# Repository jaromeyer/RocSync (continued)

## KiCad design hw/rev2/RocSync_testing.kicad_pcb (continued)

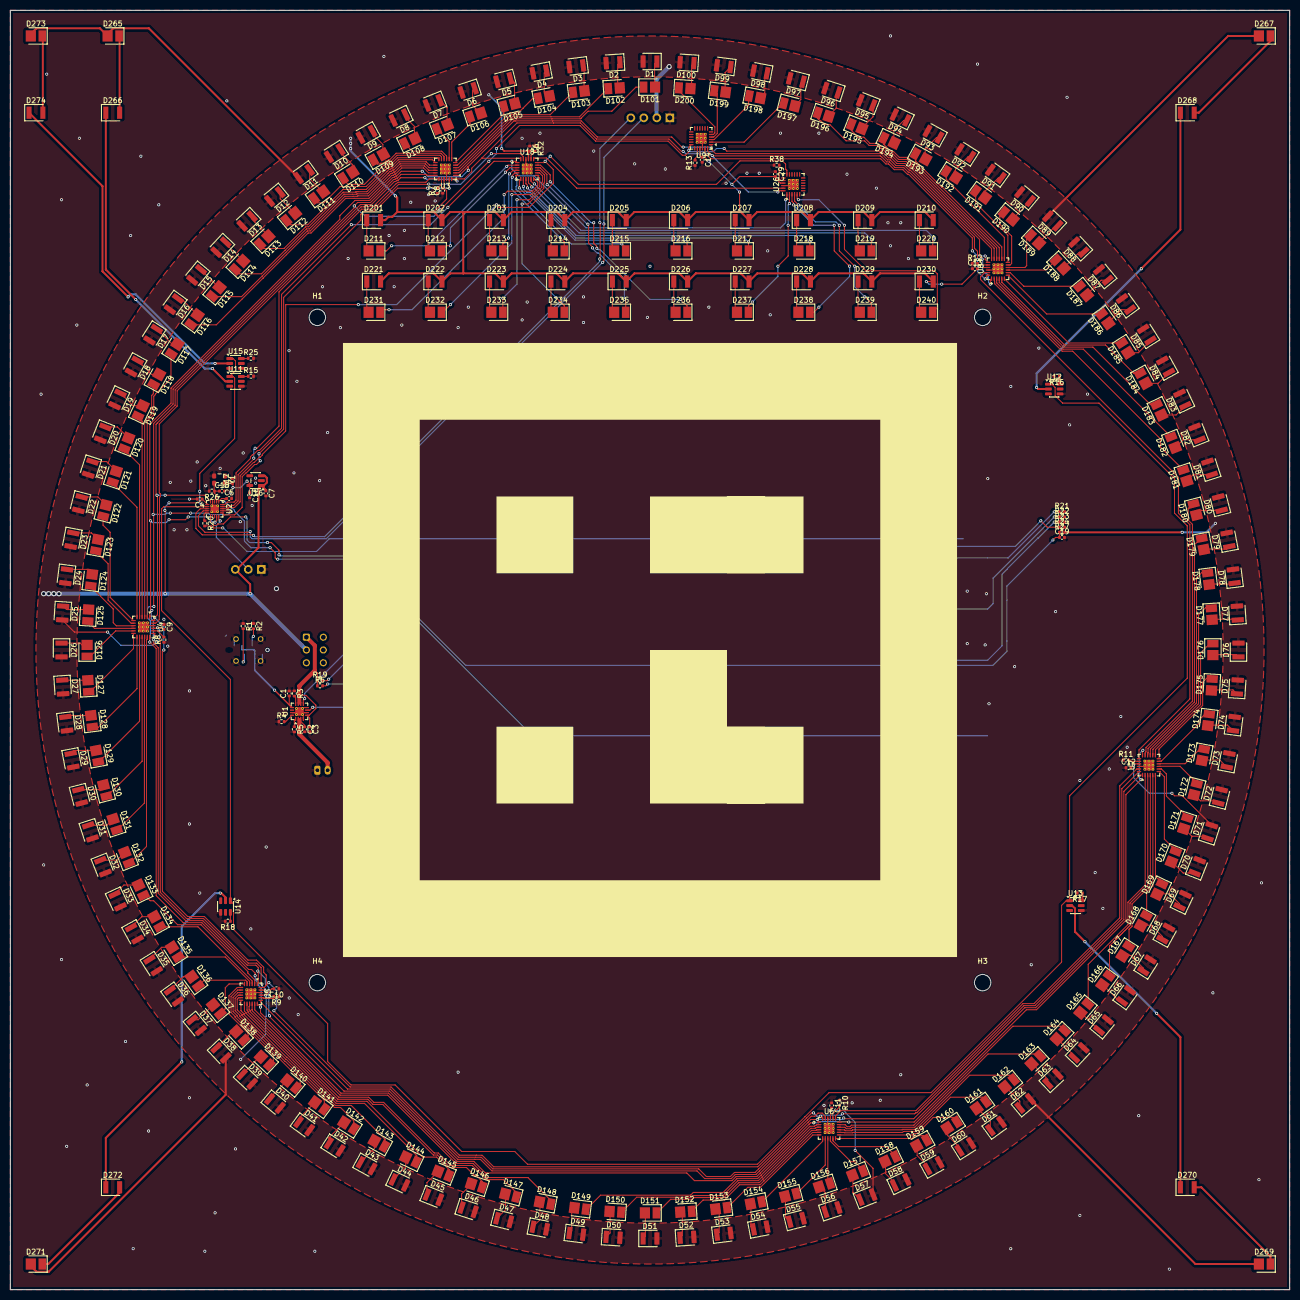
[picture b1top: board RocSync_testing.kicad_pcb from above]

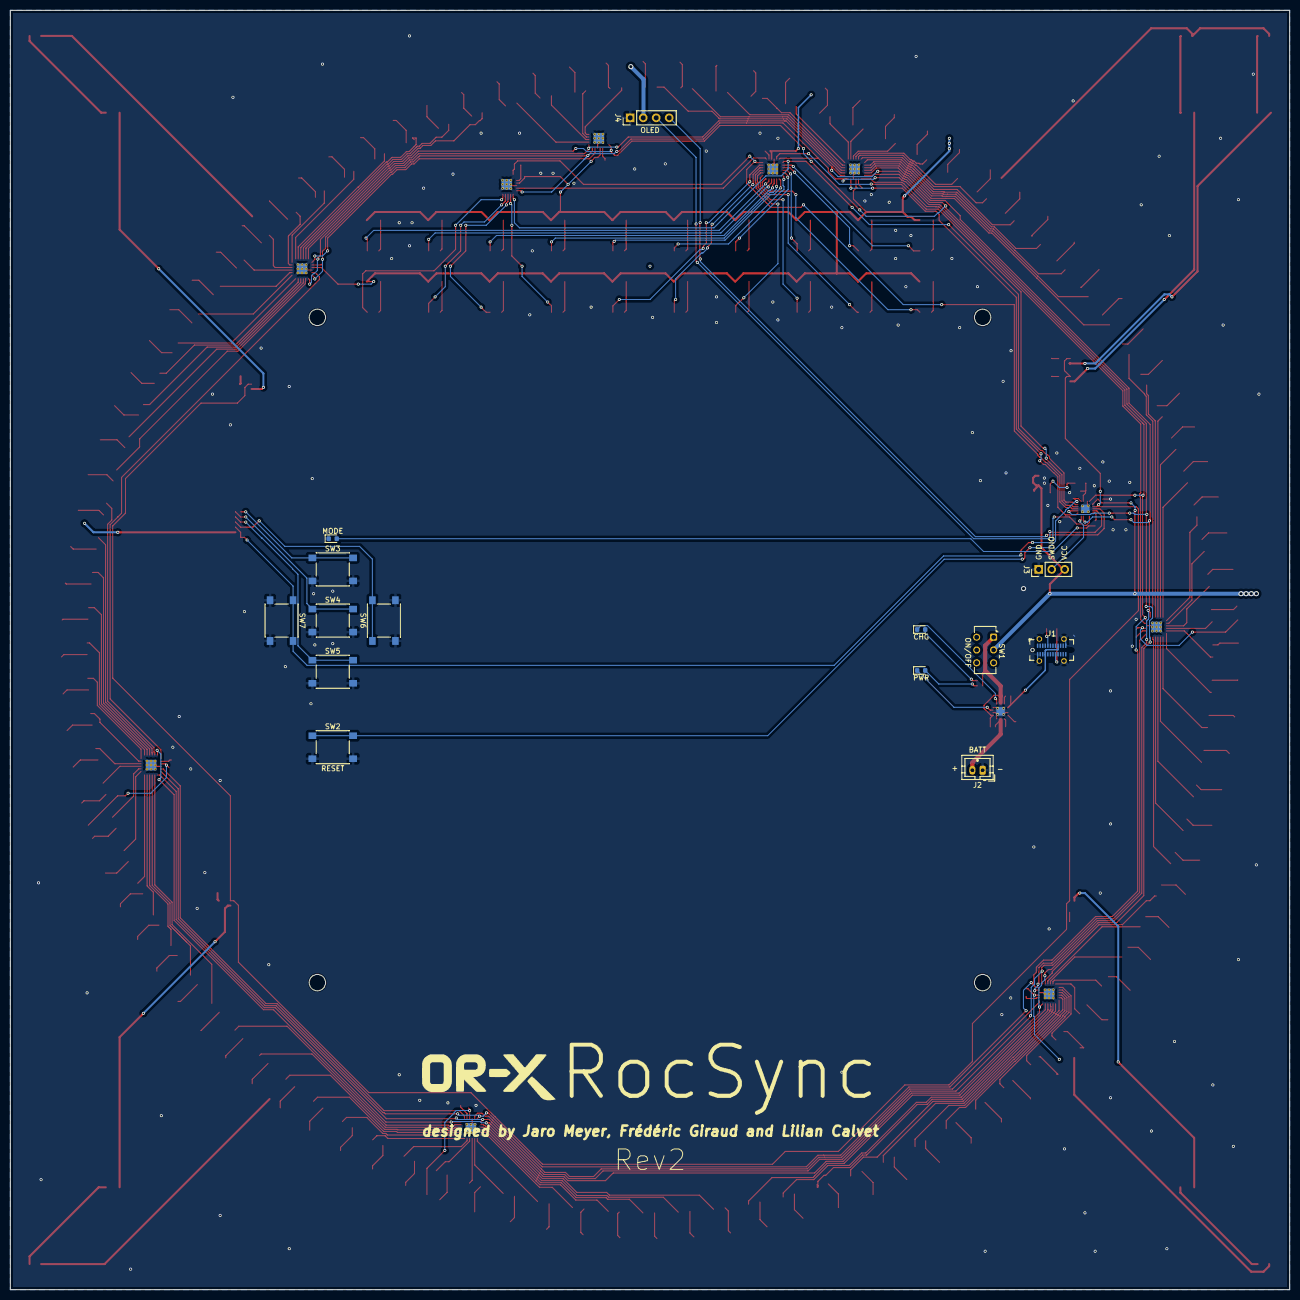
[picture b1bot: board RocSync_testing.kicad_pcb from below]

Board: 2 copper layers, 250.0 x 250.0 mm, 333 parts (14 on the bottom side), 306 nets.

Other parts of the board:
H1, H2, H3, H4: MountingHole; MountingHole_3.2mm_M3

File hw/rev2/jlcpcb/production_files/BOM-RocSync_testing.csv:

Comment,Designator,Footprint,LCSC,Quantity
0.1uf,"C10,C11,C12,C13,C14,C19,C29,C4,C5,C6,C8,C9",C_0402_1005Metric,C1525,12
1.1k,R3,R_0402_1005Metric,C25860,1
1.5k,"R19,R20,R6",R_0402_1005Metric,C25867,3
1.8k,R22,R_0402_1005Metric,C25871,1
100,"R15,R16,R17,R18,R25",R_0402_1005Metric,C25076,5
10k,"R26,R5",R_0402_1005Metric,C25744,2
10nF,C17,C_0402_1005Metric,C15195,1
10pF,C18,C_0402_1005Metric,C32949,1
1uf,"C1,C16,C7",C_0402_1005Metric,C52923,3
2.7k,"R10,R11,R12,R13,R32,R38,R7,R8,R9",R_0402_1005Metric,C25885,9
2k,R27,R_0402_1005Metric,C4109,1
4.7uf,"C2,C3",C_0402_1005Metric,C23733,2
5.1k,"R1,R2,R21",R_0402_1005Metric,C25905,3
510,R24,R_0402_1005Metric,C25123,1
590,R4,R_0402_1005Metric,C2998181,1
820,R23,R_0402_1005Metric,C25135,1
BATT,J2,JST_PH_B2B-PH-K_1x02_P2.00mm_Vertical,C594142,1
BCR420UW6Q,"U11,U12,U13,U14,U15",SOT-23-6,C194381,5
BQ24075RGT,U1,VQFN-16-1EP_3x3mm_P0.5mm_EP1.68x1.68mm_ThermalVias,C15464,1
CH32V003FxUx,U2,QFN-20-1EP_3x3mm_P0.4mm_EP1.65x1.65mm_ThermalVias,C5299908,1
CHG,D276,LED_0603_1608Metric,C2286,1
Conn_01x03_Pin,J3,PinHeader_1x03_P2.54mm_Vertical,C6332196,1
IR LED,"D101,D102,D103,D104,D105,D106,D107,D108,D109,D110,D111,D112,D113,D114,D115,D116,D117,D118,D119,D120,D121,D122,D123,D124,D125,D126,D127,D128,D129,D130,D131,D132,D133,D134,D135,D136,D137,D138,D139,D140,D141,D142,D143,D144,D145,D146,D147,D148,D149,D150,D151,D152,D153,D154,D155,D156,D157,D158,D159,D160,D161,D162,D163,D164,D165,D166,D167,D168,D169,D170,D171,D172,D173,D174,D175,D176,D177,D178,D179,D180,D181,D182,D183,D184,D185,D186,D187,D188,D189,D190,D191,D192,D193,D194,D195,D196,D197,D198,D199,D200,D211,D212,D213,D214,D215,D216,D217,D218,D219,D220,D231,D232,D233,D234,D235,D236,D237,D238,D239,D240,D265,D267,D269,D271,D273",XYC-HIR76C-LX4,C2988728,125
LED,"D1,D10,D100,D11,D12,D13,D14,D15,D16,D17,D18,D19,D2,D20,D201,D202,D203,D204,D205,D206,D207,D208,D209,D21,D210,D22,D221,D222,D223,D224,D225,D226,D227,D228,D229,D23,D230,D24,D25,D26,D266,D268,D27,D270,D272,D274,D28,D29,D3,D30,D31,D32,D33,D34,D35,D36,D37,D38,D39,D4,D40,D41,D42,D43,D44,D45,D46,D47,D48,D49,D5,D50,D51,D52,D53,D54,D55,D56,D57,D58,D59,D6,D60,D61,D62,D63,D64,D65,D66,D67,D68,D69,D7,D70,D71,D72,D73,D74,D75,D76,D77,D78,D79,D8,D80,D81,D82,D83,D84,D85,D86,D87,D88,D89,D9,D90,D91,D92,D93,D94,D95,D96,D97,D98,D99",HL-A-3528,C516141,125
MODE,D277,LED_0603_1608Metric,C2288,1
ON/OFF,SW1,SW_CK_JS202011CQN_DPDT_Straight,C431542,1
PWR,D275,LED_0603_1608Metric,C2288,1
RESET,SW2,SW_Push_1P1T_NO_6x6mm_H9.5mm,C2837531,1
SW_Push,"SW3,SW4,SW5,SW6,SW7",SW_Push_1P1T_NO_6x6mm_H9.5mm,C2837531,5
TLC59283,"U18,U26,U3,U4,U5,U6,U7,U8,U9",Texas_RGE0024C_VQFN-24-1EP_4x4mm_P0.5mm_EP2.1x2.1mm_ThermalVias,C485815,9
TPS7A2025,U16,SOT-23-5,C2869949,1
USB_C_Receptacle_PowerOnly_6P,J1,USB_C_Receptacle_GCT_USB4115-03-C,C7419862,1
huaxindianzi 2T024000VX,Y1,Oscillator_SMD_SeikoEpson_TG2520SMN-xxx-xxxxxx-4Pin_2.5x2.0mm,C47018486,1

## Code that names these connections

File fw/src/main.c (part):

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
// HW specific definitions
#if defined(REV1)
#define PIN_CLK PD0
#define PIN_RING_DATA PD2
#define PIN_RING_BLANK PD3 // T2CH2
#define PIN_RING_LATCH PC1
#define PIN_COUNTER_DATA PD5
#define PIN_COUNTER_BLANK PD4 // T2CH1ETR
#define PIN_COUNTER_LATCH PD6
#define PIN_CORNER_ENABLE PC0 // T2CH3
#define PIN_BUTTON PC2
#define PIN_MODE_LED PC3
#define COUNTER_BITS 16
#define PERIOD 100
#elif defined(REV2)
#define PIN_CLK PD0
#define PIN_RING_DATA PD2
#define PIN_RING_BLANK PD3 // T2CH2
#define PIN_RING_LATCH PC7
#define PIN_COUNTER_DATA PD5
#define PIN_COUNTER_BLANK PD4 // T2CH1ETR
#define PIN_COUNTER_LATCH PD6
#define PIN_CORNER_ENABLE PC0 // T2CH3
#define PIN_BUTTON PC4        // A2
#define PIN_MODE_LED PC3
#define COUNTER_BITS 20
#define PERIOD 100
#endif
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    if ((ticks % 2) == 0)
    {
        // falling clock edge logic
        // RING_DATA: ticks % (PERIOD * 2) == 0
        funDigitalWrite(PIN_RING_DATA, (ticks % (PERIOD * 2) == 0));

        // Counter logic
        int counter = (ticks - 1) / (PERIOD * 2) + 1;
        int index = (ticks / 2 + COUNTER_BITS - 1) % PERIOD;
        funDigitalWrite(PIN_COUNTER_DATA, (counter >> index) & 1);
    }

    // COUNTER_LATCH: ticks % (PERIOD * 2) == 1
    funDigitalWrite(PIN_COUNTER_LATCH, (ticks % (PERIOD * 2) == 1));

    // Clear the trigger state for the next IRQ
    SysTick->SR = 0x00000000;
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{
    for (int i = 0; i < COUNTER_BITS; i++)
    {
        funDigitalWrite(PIN_COUNTER_DATA, (counter >> i) & 1);
        funDigitalWrite(PIN_CLK, FUN_LOW);
        Delay_Us(1);
        funDigitalWrite(PIN_CLK, FUN_HIGH);
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
    // Setup logic outputs (Push-Pull)
    funPinMode(PIN_CLK, GPIO_Speed_10MHz | GPIO_CNF_OUT_PP);
    funPinMode(PIN_RING_DATA, GPIO_Speed_10MHz | GPIO_CNF_OUT_PP);
    funPinMode(PIN_RING_LATCH, GPIO_Speed_10MHz | GPIO_CNF_OUT_PP);
    funPinMode(PIN_COUNTER_DATA, GPIO_Speed_10MHz | GPIO_CNF_OUT_PP);
    funPinMode(PIN_COUNTER_LATCH, GPIO_Speed_10MHz | GPIO_CNF_OUT_PP);
    funPinMode(PIN_MODE_LED, GPIO_Speed_10MHz | GPIO_CNF_OUT_PP);

    // Setup brigthness PWM outputs (Alternate Function Push-Pull)
    funPinMode(PIN_RING_BLANK, GPIO_Speed_10MHz | GPIO_CNF_OUT_PP_AF);
    funPinMode(PIN_COUNTER_BLANK, GPIO_Speed_10MHz | GPIO_CNF_OUT_PP_AF);
    funPinMode(PIN_CORNER_ENABLE, GPIO_Speed_10MHz | GPIO_CNF_OUT_PP_AF);

// Setup button input
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    t2pwm_init();

    // Initial states
    funDigitalWrite(PIN_RING_DATA, FUN_LOW);
    funDigitalWrite(PIN_RING_LATCH, FUN_HIGH);
    funDigitalWrite(PIN_COUNTER_DATA, FUN_LOW);
    funDigitalWrite(PIN_COUNTER_LATCH, FUN_HIGH);
    funDigitalWrite(PIN_MODE_LED, FUN_LOW);
    set_corner_brightness(0);
    set_counter_brightness(0);
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
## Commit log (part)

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2024-09-09 add image to README
2024-09-11 Refactor CV application
2024-09-11 update readmes
2024-09-11 remove conda stuff
2024-09-11 update sw readme
2024-09-12 schematics: add note about step-up regulator
2024-09-12 sw: remove result.json
2024-09-12 sw: fix frame export
2024-09-12 sw: make threads terminate on exit
2024-09-13 sw: fix debug and frame export
2024-09-13 sw: add environment.yml
2024-09-13 sw: restructure files
2024-09-13 sw: update TODOs
2024-09-13 hw: add latest 3d models
2024-11-11 fix counter MSB always being zero
2024-11-13 fix random crashes when exporting json
2024-11-15 dont crash on skipped frame
2024-11-15 make rocsync an installable python pkg
2024-11-15 refactor video statistics
2024-11-15 also output rejected timestamps
2024-11-15 use absolute path for input files
2024-11-18 improve result printing
2024-11-18 use pathlib for handling directories
2024-11-18 add installation instructions
2024-11-18 fix error when exporting json
2024-11-18 output regression error for every considered frame
2024-11-18 make regression deterministic
2024-11-19 force regression to use > 80% of samples
2025-01-28 Add optional time windows to search for ROCsync
2025-01-28 Add better debug information
2025-01-28 Fix RANSAC algorithm
2025-02-03 Add option to directly time sync videos
2025-02-03 Small fix
2025-02-03 Add argument
2025-02-04 Use hardware acceleration if available
2025-02-04 Increase search window when ROCsync detected without valid timestamp
2025-02-20 Save intermediate results to prevent data loss on crashes
2025-03-07 Small improvements for saving
2025-03-20 Change compression type for video syncing
2025-05-02 update gitignore
2025-05-04 update hw todos
2025-05-04 add more conditions to consider a frame & allow negative timecodes for windows
2025-06-22 add initial support for ftk 3d recordings
2025-06-22 ruff format & move video ffmpeg synchronization
2025-06-22 migrate to uv
2025-06-22 refactor
2025-07-07 [fw] decrease counter brightness to improve IR detection
2025-07-07 [sw] tweak thresholds
2025-07-07 [sw] various fixes
2025-07-10 New folder evaluation that contains frame extraction script including guidelines + the manual synchronization script including the guidelines.
2025-07-21 [fw] slightly increase counter brightness again
2025-07-22 [sw] use dynamic LED thresholding & tune blob detection params
2025-07-22 [sw] remove unnecessary debug output
2025-07-23 [sw] disable blob inertia filter for now
2025-07-23 [sw] improve dynamic thresholding
2025-07-23 [sw] fix output format for single images
2025-10-08 More robust ring decoding approach that searches the most likely boundaries between ON and OFF leds
2025-10-08 Removed debug draw_result by mistake, adding it back in.
2025-10-09 Remove relative area check for aruco marker
2025-10-09 Plot timestamps for ftk in debug mode
2025-10-13 Formatting of warnings, require at least two timestamps for linear regression.
2025-12-09 [hw] rev 2
2025-12-10 [fw] update pin definitions for rev2 and initialize HSE in bypass mode
2026-01-22 added back some local files to the fork of jaro's repo (mostly the extract clips as ... scripts)
2026-01-22 updated fw readme
2026-01-22 improved synced videos file and readme
2026-01-23 Added unittest for new RGB LED decoding (RGB tested, works, IR not tested)
2026-01-23 updated cover model (stl and step) for new led layout
2026-01-23 firmware updates (only led cound updated, analogRead for the buttons still broken)
2026-02-03 added functionalities for extraction script
2026-02-23 updated extract synced videos
2026-02-23 deleted manual synch files
2026-03-19 [fw] switch to ch32fun & add config for both hw revisions
2026-03-19 [hw] add kicad and production files for rev2
2026-03-20 [fw] update README
2026-03-20 [fw] fix fiducial filtering
2026-03-20 fix paper link
2026-03-21 [misc] add marker geometry specification for both revisions
2026-03-21 [README] add note about geometry files
2026-03-21 [hw] move headers to back layer to fix 3D render
2026-03-23 [hw] add note about HSE bypass
2026-04-01 added try_hard mode that refines the rectification using both the aruco corners and led corners. allows for missing led corners.
2026-04-01 improve instructions
2026-04-11 improved output formatting
2026-04-11 removed try-hard argument to keep PRs separate
2026-04-11 added benchmark hooks and scripts to evaluate implementation changes on reference images.
2026-04-11 compare predictions against ground-truth annotations. bugfixes.
2026-04-11 bugfixes
2026-04-11 code cleanup
2026-04-11 Benchmark submodule with annotation tool
2026-04-11 timings formatting fix. give user control over which methods are compared in the evaluation.
2026-04-11 WIP: Implementing BoardProfiles to support rocsync v1 and v2
2026-04-11 simplified corner position parsing
2026-04-11 corners superimposed in original and rectified image
2026-04-11 Make benchmark tools compatible with backwards compatibility changes
2026-06-29 feat: add configurable image preprocessing options
    Add --alpha to define the lower normalization bound
    Add --beta to define the upper normalization bound
    Add --gamma to apply gamma correction to pixel values
    Add --debug_preprocessing to display images before and after preprocessing
    This allows preprocessing parameters to be adjusted before running the full synchronization.
2026-06-29 bug in find corners aruco. input variable is named normalization and not normalization_bounds
2026-06-29 Updated help messages
